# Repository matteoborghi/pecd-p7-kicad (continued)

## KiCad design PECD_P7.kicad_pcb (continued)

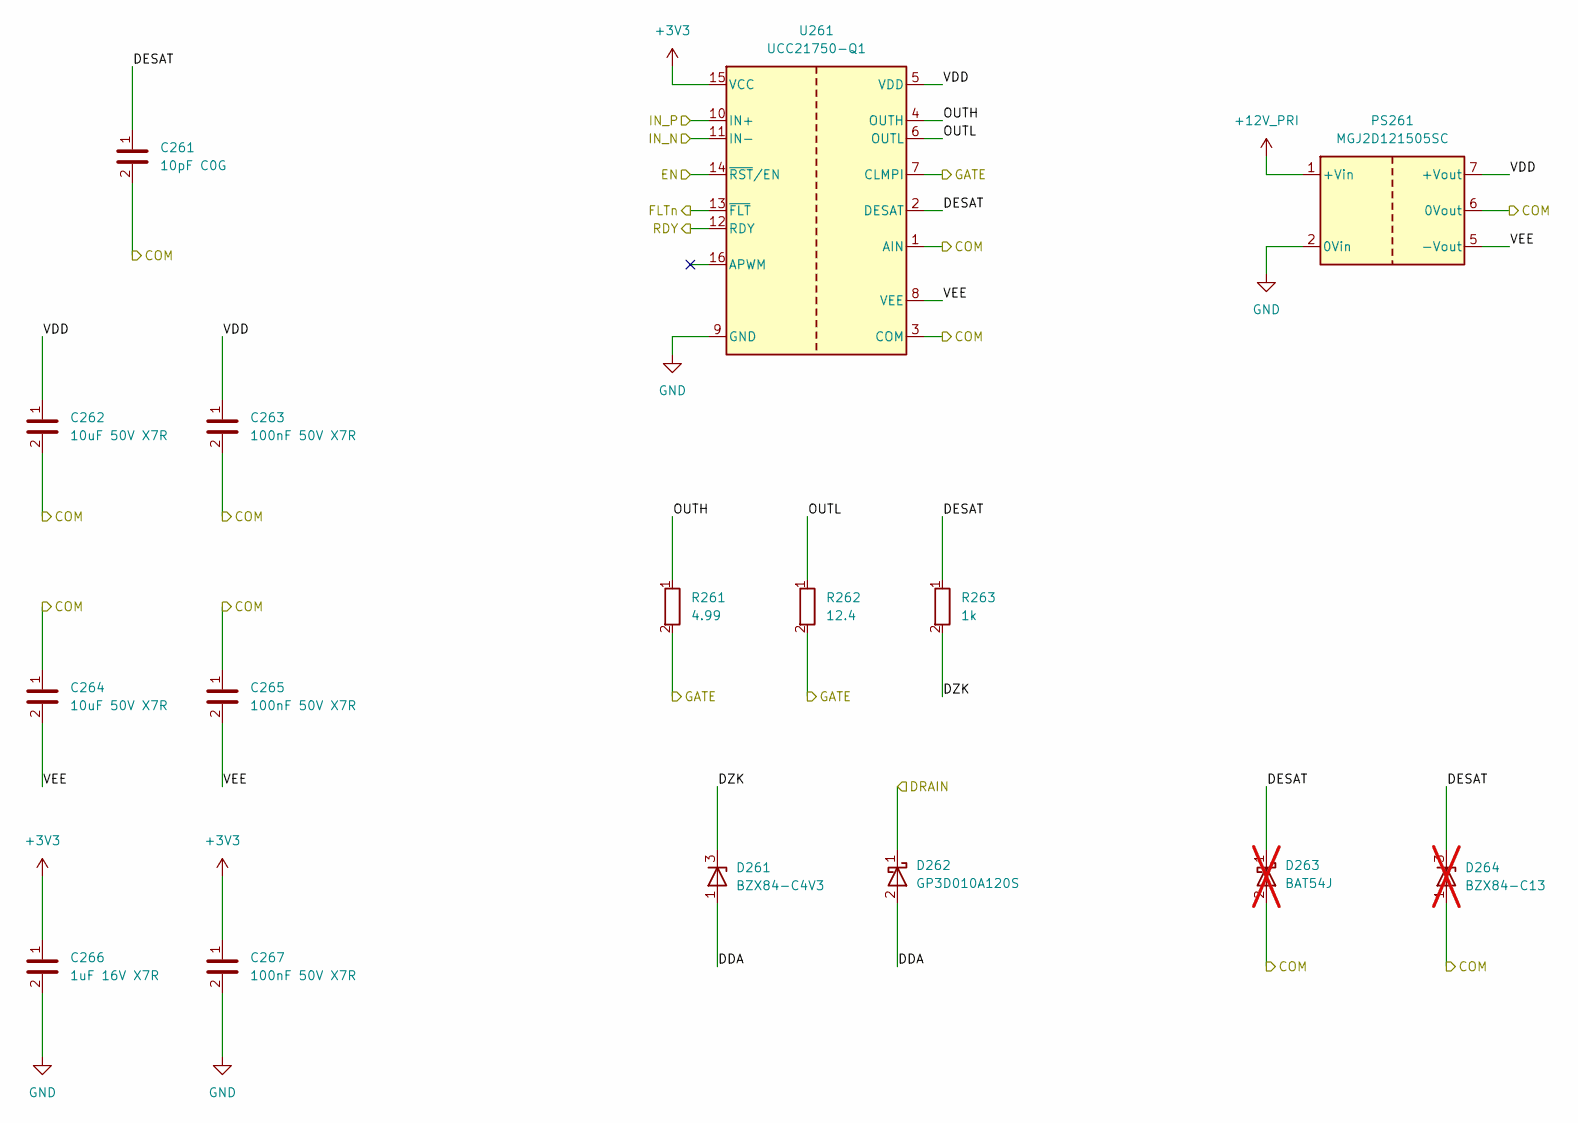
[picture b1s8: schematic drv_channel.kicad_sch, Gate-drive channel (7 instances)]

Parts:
C261: 10pF C0G; C_0603_1608Metric; MPN GCM1885C1H100JA16D
C262, C264: 10uF 50V X7R; C_1210_3225Metric; MPN GRM32ER71H106KA12L
C263, C265, C267: 100nF 50V X7R; C_0603_1608Metric; MPN GCM188R71H104KA57D
C266: 1uF 16V X7R; C_0603_1608Metric; MPN GCM188R71C105KA64D
D261: BZX84-C4V3; SOT-23; MPN BZX84-C4V3,215
D262: GP3D010A120S; D_SMC_HV; MPN GP3D010A120S
D263: BAT54J; D_SOD-323F; MPN BAT54J,115; not fitted
D264: BZX84-C13; SOT-23; MPN BZX84-C13,215; not fitted
PS261: MGJ2D121505SC; MGJ2_SIP7; MPN MGJ2D121505SC
R261: 4.99; R_1206_3216Metric; MPN CRCW12064R99FKEAHP
R262: 12.4; R_1206_3216Metric; MPN ERJ-P08F12R4V
R263: 1k; R_0603_1608Metric; MPN ERJ-3EKF1001V
U261: UCC21750-Q1; SOIC-16W_TI_DW_HV_Slot; MPN UCC21750QDWRQ1

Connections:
+3V3: C266.1, C267.1, U261.15 (VCC); also elsewhere on the board
+12V_PRI: PS261.1 (+Vin); also elsewhere on the board
/2_gate_drive/drv_L3/DDA: D261.1 (A), D262.2 (A)
/2_gate_drive/drv_L3/DESAT: C261.1, D263.1 (K), D264.3 (K), R263.1, U261.2 (DESAT)
/2_gate_drive/drv_L3/DZK: D261.3 (K), R263.2
/2_gate_drive/drv_L3/OUTH: R261.1, U261.4 (OUTH)
/2_gate_drive/drv_L3/OUTL: R262.1, U261.6 (OUTL)
/2_gate_drive/drv_L3/VDD: C262.1, C263.1, PS261.7 (+Vout), U261.5 (VDD)
/2_gate_drive/drv_L3/VEE: C264.2, C265.2, PS261.5 (-Vout), U261.8 (VEE)
/CTL_EN: U261.14 (~RST/EN); also elsewhere on the board
/CTL_FLTn: U261.13 (~FLT); also elsewhere on the board
/CTL_PWM_H3: U261.11 (IN-); also elsewhere on the board
/CTL_PWM_L3: U261.10 (IN+); also elsewhere on the board
/CTL_RDY: U261.12 (RDY); also elsewhere on the board
/GL3_COM: C261.2, C262.2, C263.2, C264.1, C265.1, D263.2 (A), D264.1 (A), PS261.6 (0Vout), U261.1 (AIN), U261.3 (COM); also elsewhere on the board
/GL3_GATE: R261.2, R262.2, U261.7 (CLMPI); also elsewhere on the board
/HV_SW3: D262.1 (K); also elsewhere on the board
GND: C266.2, C267.2, PS261.2 (0Vin), U261.9 (GND); also elsewhere on the board

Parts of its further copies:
C211, C221, C231, C241, C251, C681: 10pF C0G; C_0603_1608Metric; MPN GCM1885C1H100JA16D
C212, C214, C222, C224, C232, C234, C242, C244, C252, C254, C682, C684: 10uF 50V X7R; C_1210_3225Metric; MPN GRM32ER71H106KA12L
C213, C215, C217, C223, C225, C227, C233, C235, C237, C243, C245, C247, C253, C255, C257, C683, C685, C687: 100nF 50V X7R; C_0603_1608Metric; MPN GCM188R71H104KA57D
C216, C226, C236, C246, C256, C686: 1uF 16V X7R; C_0603_1608Metric; MPN GCM188R71C105KA64D
D211, D221, D231, D241, D251, D681: BZX84-C4V3; SOT-23; MPN BZX84-C4V3,215
D212, D222, D232, D242, D252, D682: GP3D010A120S; D_SMC_HV; MPN GP3D010A120S
D213, D223, D233, D243, D253, D683: BAT54J; D_SOD-323F; MPN BAT54J,115; not fitted
D214, D224, D234, D244, D254, D684: BZX84-C13; SOT-23; MPN BZX84-C13,215; not fitted
PS211, PS221, PS231, PS241, PS251, PS681: MGJ2D121505SC; MGJ2_SIP7; MPN MGJ2D121505SC
R211, R221, R231, R241, R251, R681: 4.99; R_1206_3216Metric; MPN CRCW12064R99FKEAHP
R212, R222, R232, R242, R252, R682: 12.4; R_1206_3216Metric; MPN ERJ-P08F12R4V
R213, R223, R233, R243, R253, R683: 1k; R_0603_1608Metric; MPN ERJ-3EKF1001V
U211, U221, U231, U241, U251, U681: UCC21750-Q1; SOIC-16W_TI_DW_HV_Slot; MPN UCC21750QDWRQ1

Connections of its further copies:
+3V3: C216.1, C217.1, C226.1, C227.1, C236.1, C237.1, C246.1, C247.1, C256.1, C257.1, C686.1, C687.1, U211.15 (VCC), U221.15 (VCC), U231.15 (VCC), U241.15 (VCC), U251.15 (VCC), U681.15 (VCC); also elsewhere on the board
+12V_PRI: PS211.1 (+Vin), PS221.1 (+Vin), PS231.1 (+Vin), PS241.1 (+Vin), PS251.1 (+Vin), PS681.1 (+Vin); also elsewhere on the board
/2_gate_drive/drv_H1/DDA: D211.1 (A), D212.2 (A)
/2_gate_drive/drv_H1/DESAT: C211.1, D213.1 (K), D214.3 (K), R213.1, U211.2 (DESAT)
/2_gate_drive/drv_H1/DZK: D211.3 (K), R213.2
/2_gate_drive/drv_H1/OUTH: R211.1, U211.4 (OUTH)
/2_gate_drive/drv_H1/OUTL: R212.1, U211.6 (OUTL)
/2_gate_drive/drv_H1/VDD: C212.1, C213.1, PS211.7 (+Vout), U211.5 (VDD)
/2_gate_drive/drv_H1/VEE: C214.2, C215.2, PS211.5 (-Vout), U211.8 (VEE)
/2_gate_drive/drv_H2/DDA: D231.1 (A), D232.2 (A)
/2_gate_drive/drv_H2/DESAT: C231.1, D233.1 (K), D234.3 (K), R233.1, U231.2 (DESAT)
/2_gate_drive/drv_H2/DZK: D231.3 (K), R233.2
/2_gate_drive/drv_H2/OUTH: R231.1, U231.4 (OUTH)
/2_gate_drive/drv_H2/OUTL: R232.1, U231.6 (OUTL)
/2_gate_drive/drv_H2/VDD: C232.1, C233.1, PS231.7 (+Vout), U231.5 (VDD)
/2_gate_drive/drv_H2/VEE: C234.2, C235.2, PS231.5 (-Vout), U231.8 (VEE)
/2_gate_drive/drv_H3/DDA: D251.1 (A), D252.2 (A)
/2_gate_drive/drv_H3/DESAT: C251.1, D253.1 (K), D254.3 (K), R253.1, U251.2 (DESAT)
/2_gate_drive/drv_H3/DZK: D251.3 (K), R253.2
/2_gate_drive/drv_H3/OUTH: R251.1, U251.4 (OUTH)
/2_gate_drive/drv_H3/OUTL: R252.1, U251.6 (OUTL)
/2_gate_drive/drv_H3/VDD: C252.1, C253.1, PS251.7 (+Vout), U251.5 (VDD)
/2_gate_drive/drv_H3/VEE: C254.2, C255.2, PS251.5 (-Vout), U251.8 (VEE)
/2_gate_drive/drv_L1/DDA: D221.1 (A), D222.2 (A)
/2_gate_drive/drv_L1/DESAT: C221.1, D223.1 (K), D224.3 (K), R223.1, U221.2 (DESAT)
/2_gate_drive/drv_L1/DZK: D221.3 (K), R223.2
/2_gate_drive/drv_L1/OUTH: R221.1, U221.4 (OUTH)
/2_gate_drive/drv_L1/OUTL: R222.1, U221.6 (OUTL)
/2_gate_drive/drv_L1/VDD: C222.1, C223.1, PS221.7 (+Vout), U221.5 (VDD)
/2_gate_drive/drv_L1/VEE: C224.2, C225.2, PS221.5 (-Vout), U221.8 (VEE)
/2_gate_drive/drv_L2/DDA: D241.1 (A), D242.2 (A)
/2_gate_drive/drv_L2/DESAT: C241.1, D243.1 (K), D244.3 (K), R243.1, U241.2 (DESAT)
/2_gate_drive/drv_L2/DZK: D241.3 (K), R243.2
/2_gate_drive/drv_L2/OUTH: R241.1, U241.4 (OUTH)
/2_gate_drive/drv_L2/OUTL: R242.1, U241.6 (OUTL)
/2_gate_drive/drv_L2/VDD: C242.1, C243.1, PS241.7 (+Vout), U241.5 (VDD)
/2_gate_drive/drv_L2/VEE: C244.2, C245.2, PS241.5 (-Vout), U241.8 (VEE)
/6_dclink_mgmt/GDIS_COM: C681.2, C682.2, C683.2, C684.1, C685.1, D682.1 (K), D683.2 (A), D684.1 (A), PS681.6 (0Vout), U681.1 (AIN), U681.3 (COM); also elsewhere on the board
/6_dclink_mgmt/GDIS_GATE: R681.2, R682.2, U681.7 (CLMPI); also elsewhere on the board
/6_dclink_mgmt/drv_DIS/DDA: D681.1 (A), D682.2 (A)
/6_dclink_mgmt/drv_DIS/DESAT: C681.1, D683.1 (K), D684.3 (K), R683.1, U681.2 (DESAT)
/6_dclink_mgmt/drv_DIS/DZK: D681.3 (K), R683.2
/6_dclink_mgmt/drv_DIS/OUTH: R681.1, U681.4 (OUTH)
/6_dclink_mgmt/drv_DIS/OUTL: R682.1, U681.6 (OUTL)
/6_dclink_mgmt/drv_DIS/VDD: C682.1, C683.1, PS681.7 (+Vout), U681.5 (VDD)
/6_dclink_mgmt/drv_DIS/VEE: C684.2, C685.2, PS681.5 (-Vout), U681.8 (VEE)
/CTL_DISCH_EN: U681.10 (IN+); also elsewhere on the board
/CTL_EN: U211.14 (~RST/EN), U221.14 (~RST/EN), U231.14 (~RST/EN), U241.14 (~RST/EN), U251.14 (~RST/EN), U681.14 (~RST/EN); also elsewhere on the board
/CTL_FLTn: U211.13 (~FLT), U221.13 (~FLT), U231.13 (~FLT), U241.13 (~FLT), U251.13 (~FLT), U681.13 (~FLT); also elsewhere on the board
/CTL_PWM_H1: U211.10 (IN+), U221.11 (IN-); also elsewhere on the board
/CTL_PWM_H2: U231.10 (IN+), U241.11 (IN-); also elsewhere on the board
/CTL_PWM_H3: U251.10 (IN+); also elsewhere on the board
/CTL_PWM_L1: U211.11 (IN-), U221.10 (IN+); also elsewhere on the board
/CTL_PWM_L2: U231.11 (IN-), U241.10 (IN+); also elsewhere on the board
/CTL_PWM_L3: U251.11 (IN-); also elsewhere on the board
/CTL_RDY: U211.12 (RDY), U221.12 (RDY), U231.12 (RDY), U241.12 (RDY), U251.12 (RDY), U681.12 (RDY); also elsewhere on the board
/GH1_COM: C211.2, C212.2, C213.2, C214.1, C215.1, D213.2 (A), D214.1 (A), PS211.6 (0Vout), U211.1 (AIN), U211.3 (COM); also elsewhere on the board
/GH1_GATE: R211.2, R212.2, U211.7 (CLMPI); also elsewhere on the board
/GH2_COM: C231.2, C232.2, C233.2, C234.1, C235.1, D233.2 (A), D234.1 (A), PS231.6 (0Vout), U231.1 (AIN), U231.3 (COM); also elsewhere on the board
/GH2_GATE: R231.2, R232.2, U231.7 (CLMPI); also elsewhere on the board
/GH3_COM: C251.2, C252.2, C253.2, C254.1, C255.1, D253.2 (A), D254.1 (A), PS251.6 (0Vout), U251.1 (AIN), U251.3 (COM); also elsewhere on the board
/GH3_GATE: R251.2, R252.2, U251.7 (CLMPI); also elsewhere on the board
/GL1_COM: C221.2, C222.2, C223.2, C224.1, C225.1, D223.2 (A), D224.1 (A), PS221.6 (0Vout), U221.1 (AIN), U221.3 (COM); also elsewhere on the board
/GL1_GATE: R221.2, R222.2, U221.7 (CLMPI); also elsewhere on the board
/GL2_COM: C241.2, C242.2, C243.2, C244.1, C245.1, D243.2 (A), D244.1 (A), PS241.6 (0Vout), U241.1 (AIN), U241.3 (COM); also elsewhere on the board
/GL2_GATE: R241.2, R242.2, U241.7 (CLMPI); also elsewhere on the board
/HV_DCP: D212.1 (K), D232.1 (K), D252.1 (K); also elsewhere on the board
/HV_SW1: D222.1 (K); also elsewhere on the board
/HV_SW2: D242.1 (K); also elsewhere on the board
GND: C216.2, C217.2, C226.2, C227.2, C236.2, C237.2, C246.2, C247.2, C256.2, C257.2, C686.2, C687.2, PS211.2 (0Vin), PS221.2 (0Vin), PS231.2 (0Vin), PS241.2 (0Vin), PS251.2 (0Vin), PS681.2 (0Vin), U211.9 (GND), U221.9 (GND), U231.9 (GND), U241.9 (GND), U251.9 (GND), U681.9 (GND), U681.11 (IN-); also elsewhere on the board

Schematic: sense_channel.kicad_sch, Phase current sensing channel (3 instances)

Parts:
C321, C324, C326: 100nF 50V X7R; C_0603_1608Metric; MPN GCM188R71H104KA57D
C322: 10uF 50V X7R; C_1210_3225Metric; MPN GRM32ER71H106KA12L
C323, C325: 1uF 16V X7R; C_0603_1608Metric; MPN GCM188R71C105KA64D
C327: 22nF C0G; C_0805_2012Metric; MPN GCM21B5C1H223JA16L
C328, C329: 100pF C0G; C_0603_1608Metric; MPN GCM1885C1H101JA16D
C330: 15nF C0G; C_0805_2012Metric; MPN GCM2195C1H153JA16D
NT321: NetTie; NetTie-2_SMD_Pad0.5mm
PS321: MGJ2D121505SC; MGJ2_SIP7; MPN MGJ2D121505SC
R321, R322: 2.2; R_0603_1608Metric; MPN ERJ-3RQF2R2V
R323, R324: 49.9; R_0603_1608Metric; MPN ERJ-3EKF49R9V
U321: AMC1302-Q1; SOIC-8W_TI_DWV_Slot; MPN AMC1302QDWVRQ1
U322: TPS7B6950-Q1; SOT-23-5; MPN TPS7B6950QDBVRQ1

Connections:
+3V3: C325.1, C326.1, U321.8 (VDD2); also elsewhere on the board
+12V_PRI: PS321.1 (+Vin); also elsewhere on the board
/3_phase_sense/I1N_RAW: R324.1, U321.6 (OUTN); also elsewhere on the board
/3_phase_sense/I1P_RAW: R323.1, U321.7 (OUTP); also elsewhere on the board
/3_phase_sense/sense_1/GND1: C321.2, C322.2, C323.2, C324.2, C328.2, C329.2, NT321.2, PS321.6 (0Vout), U321.4 (GND1), U322.3 (GND), U322.4 (GND)
/3_phase_sense/sense_1/INN: C327.2, C329.1, R322.2, U321.3 (INN)
/3_phase_sense/sense_1/INP: C327.1, C328.1, R321.2, U321.2 (INP)
/3_phase_sense/sense_1/VDD1: C322.1, C323.1, C324.1, U321.1 (VDD1), U322.5 (OUT)
/3_phase_sense/sense_1/VISO: C321.1, PS321.7 (+Vout), U322.1 (IN)
/CTL_I1N: C330.2, R324.2; also elsewhere on the board
/CTL_I1P: C330.1, R323.2; also elsewhere on the board
/SNS1_SN: NT321.1, R322.1; also elsewhere on the board
/SNS1_SP: R321.1; also elsewhere on the board
GND: C325.2, C326.2, PS321.2 (0Vin), U321.5 (GND2); also elsewhere on the board

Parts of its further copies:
C341, C344, C346, C361, C364, C366: 100nF 50V X7R; C_0603_1608Metric; MPN GCM188R71H104KA57D
C342, C362: 10uF 50V X7R; C_1210_3225Metric; MPN GRM32ER71H106KA12L
C343, C345, C363, C365: 1uF 16V X7R; C_0603_1608Metric; MPN GCM188R71C105KA64D
C347, C367: 22nF C0G; C_0805_2012Metric; MPN GCM21B5C1H223JA16L
C348, C349, C368, C369: 100pF C0G; C_0603_1608Metric; MPN GCM1885C1H101JA16D
C350, C370: 15nF C0G; C_0805_2012Metric; MPN GCM2195C1H153JA16D
NT341, NT361: NetTie; NetTie-2_SMD_Pad0.5mm
PS341, PS361: MGJ2D121505SC; MGJ2_SIP7; MPN MGJ2D121505SC
R341, R342, R361, R362: 2.2; R_0603_1608Metric; MPN ERJ-3RQF2R2V
R343, R344, R363, R364: 49.9; R_0603_1608Metric; MPN ERJ-3EKF49R9V
U341, U361: AMC1302-Q1; SOIC-8W_TI_DWV_Slot; MPN AMC1302QDWVRQ1
U342, U362: TPS7B6950-Q1; SOT-23-5; MPN TPS7B6950QDBVRQ1

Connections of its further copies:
+3V3: C345.1, C346.1, C365.1, C366.1, U341.8 (VDD2), U361.8 (VDD2); also elsewhere on the board
+12V_PRI: PS341.1 (+Vin), PS361.1 (+Vin); also elsewhere on the board
/3_phase_sense/I2N_RAW: R344.1, U341.6 (OUTN); also elsewhere on the board
/3_phase_sense/I2P_RAW: R343.1, U341.7 (OUTP); also elsewhere on the board
/3_phase_sense/I3N_RAW: R364.1, U361.6 (OUTN); also elsewhere on the board
/3_phase_sense/I3P_RAW: R363.1, U361.7 (OUTP); also elsewhere on the board
/3_phase_sense/sense_2/GND1: C341.2, C342.2, C343.2, C344.2, C348.2, C349.2, NT341.2, PS341.6 (0Vout), U341.4 (GND1), U342.3 (GND), U342.4 (GND)
/3_phase_sense/sense_2/INN: C347.2, C349.1, R342.2, U341.3 (INN)
/3_phase_sense/sense_2/INP: C347.1, C348.1, R341.2, U341.2 (INP)
/3_phase_sense/sense_2/VDD1: C342.1, C343.1, C344.1, U341.1 (VDD1), U342.5 (OUT)
/3_phase_sense/sense_2/VISO: C341.1, PS341.7 (+Vout), U342.1 (IN)
/3_phase_sense/sense_3/GND1: C361.2, C362.2, C363.2, C364.2, C368.2, C369.2, NT361.2, PS361.6 (0Vout), U361.4 (GND1), U362.3 (GND), U362.4 (GND)
/3_phase_sense/sense_3/INN: C367.2, C369.1, R362.2, U361.3 (INN)
/3_phase_sense/sense_3/INP: C367.1, C368.1, R361.2, U361.2 (INP)
/3_phase_sense/sense_3/VDD1: C362.1, C363.1, C364.1, U361.1 (VDD1), U362.5 (OUT)
/3_phase_sense/sense_3/VISO: C361.1, PS361.7 (+Vout), U362.1 (IN)
/CTL_I2N: C350.2, R344.2; also elsewhere on the board
/CTL_I2P: C350.1, R343.2; also elsewhere on the board
/CTL_I3N: C370.2, R364.2; also elsewhere on the board
/CTL_I3P: C370.1, R363.2; also elsewhere on the board
/SNS2_SN: NT341.1, R342.1; also elsewhere on the board
/SNS2_SP: R341.1; also elsewhere on the board
/SNS3_SN: NT361.1, R362.1; also elsewhere on the board
/SNS3_SP: R361.1; also elsewhere on the board
GND: C345.2, C346.2, C365.2, C366.2, PS341.2 (0Vin), PS361.2 (0Vin), U341.5 (GND2), U361.5 (GND2); also elsewhere on the board

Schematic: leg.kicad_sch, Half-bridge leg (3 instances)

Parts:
C131, C132, C133, C134: 47nF 1200V C0G; C_3640_9110Metric; MPN CKC33C473KEGACAUTO
Q131, Q132: E3M0016120K; TO-247-4L_Wolfspeed_Vertical; MPN E3M0016120K
R131: CSS2H-3920R-L500FE; R_Shunt_3920_Kelvin; MPN CSS2H-3920R-L500FE

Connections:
/1_power_stage/HV_PH3: R131.2; also elsewhere on the board
/GH3_COM: Q131.3 (S_K); also elsewhere on the board
/GH3_GATE: Q131.4 (G); also elsewhere on the board
/GL3_COM: Q132.3 (S_K); also elsewhere on the board
/GL3_GATE: Q132.4 (G); also elsewhere on the board
/HV_DCN: C131.2, C132.2, C133.2, C134.2, Q132.2 (S); also elsewhere on the board
/HV_DCP: C131.1, C132.1, C133.1, C134.1, Q131.1 (D); also elsewhere on the board
/HV_SW3: Q131.2 (S), Q132.1 (D), R131.1; also elsewhere on the board
/SNS3_SN: R131.4 (S2); also elsewhere on the board
/SNS3_SP: R131.3 (S1); also elsewhere on the board

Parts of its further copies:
C111, C112, C113, C114, C121, C122, C123, C124: 47nF 1200V C0G; C_3640_9110Metric; MPN CKC33C473KEGACAUTO
Q111, Q112, Q121, Q122: E3M0016120K; TO-247-4L_Wolfspeed_Vertical; MPN E3M0016120K
R111, R121: CSS2H-3920R-L500FE; R_Shunt_3920_Kelvin; MPN CSS2H-3920R-L500FE

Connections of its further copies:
/1_power_stage/HV_PH1: R111.2; also elsewhere on the board
/1_power_stage/HV_PH2: R121.2; also elsewhere on the board
/GH1_COM: Q111.3 (S_K); also elsewhere on the board
/GH1_GATE: Q111.4 (G); also elsewhere on the board
/GH2_COM: Q121.3 (S_K); also elsewhere on the board
/GH2_GATE: Q121.4 (G); also elsewhere on the board
/GL1_COM: Q112.3 (S_K); also elsewhere on the board
/GL1_GATE: Q112.4 (G); also elsewhere on the board
/GL2_COM: Q122.3 (S_K); also elsewhere on the board
/GL2_GATE: Q122.4 (G); also elsewhere on the board
/HV_DCN: C111.2, C112.2, C113.2, C114.2, C121.2, C122.2, C123.2, C124.2, Q112.2 (S), Q122.2 (S); also elsewhere on the board
/HV_DCP: C111.1, C112.1, C113.1, C114.1, C121.1, C122.1, C123.1, C124.1, Q111.1 (D), Q121.1 (D); also elsewhere on the board
/HV_SW1: Q111.2 (S), Q112.1 (D), R111.1; also elsewhere on the board
/HV_SW2: Q121.2 (S), Q122.1 (D), R121.1; also elsewhere on the board
/SNS1_SN: R111.4 (S2); also elsewhere on the board
/SNS1_SP: R111.3 (S1); also elsewhere on the board
/SNS2_SN: R121.4 (S2); also elsewhere on the board
/SNS2_SP: R121.3 (S1); also elsewhere on the board

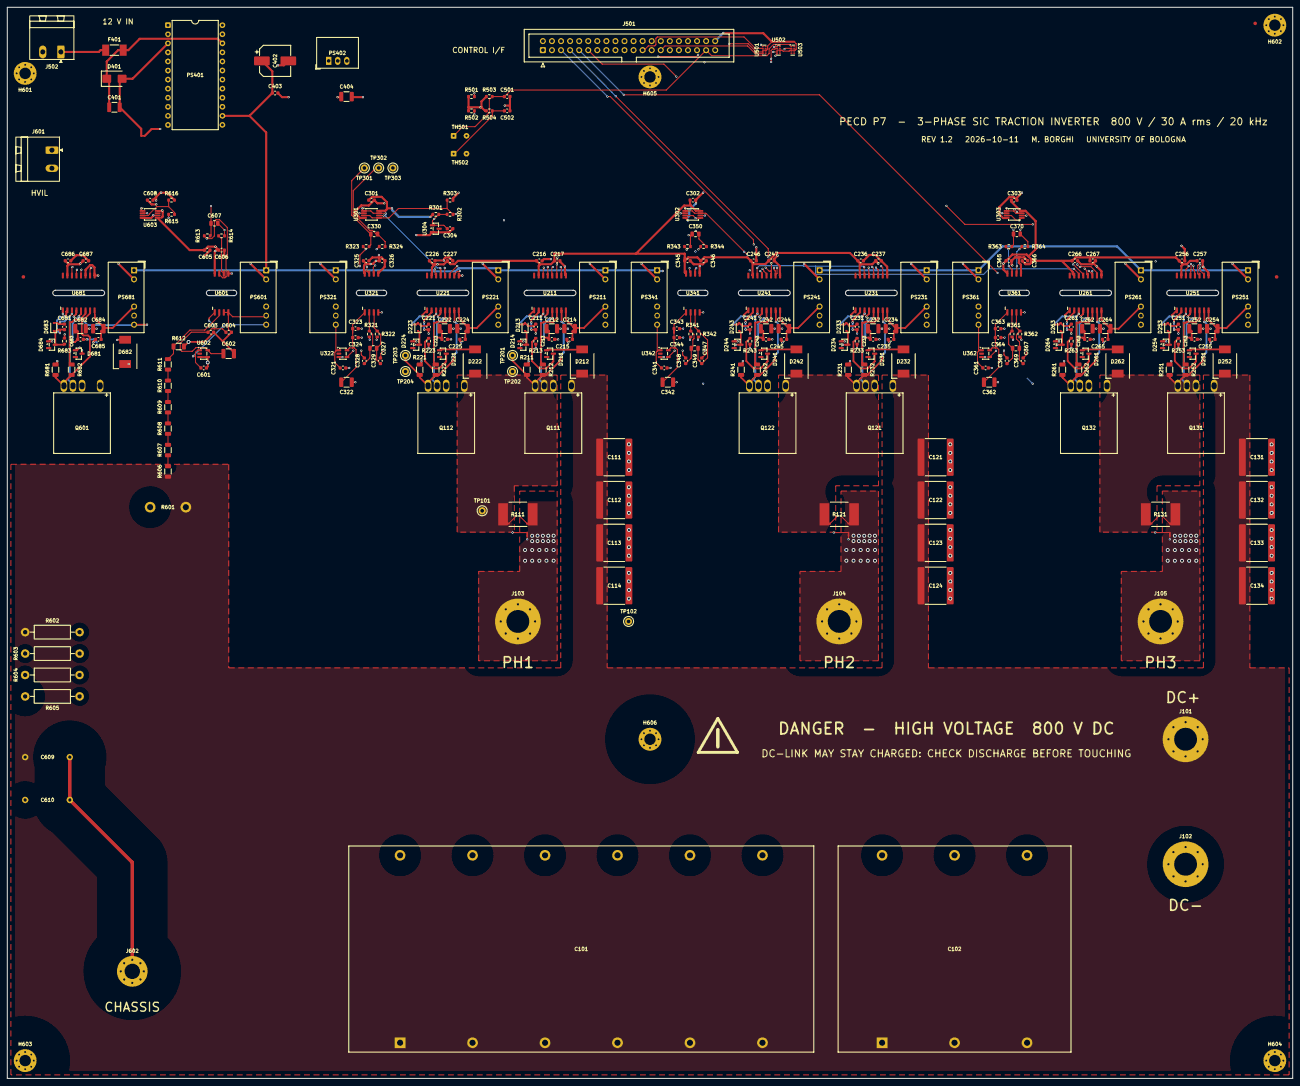
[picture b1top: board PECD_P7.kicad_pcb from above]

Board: 6 copper layers, 360.0 x 300.0 mm, 278 parts (0 on the bottom side), 143 nets.

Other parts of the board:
FID1, FID2, FID3: Fiducial_1mm_Mask2mm
